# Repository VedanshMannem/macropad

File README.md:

# Setup

1) Set up [OPL Libary](https://github.com/Seeed-Studio/OPL_Kicad_Library/)
2) Add this for the [OLED footprints](https://gi1thub.com/gorbachev/KiCad-SSD1306-0.91-OLED-4pin-128x32.pretty/blob/master/SSD1306-0.91-OLED-4pin-128x32.kicad_mod)
3) Download all the project files into KiCad/Fusion or whatever system you use and you can edit however

Materials (No BOM):
- 4x Cherry MX Switches
- 6x SK6812 MINI Leds
- 1x XIAO RP2040
- 4x Blank DSA Keycaps
- 4x M3x16 Bolt
- 4x M3 Heatset
- 1x OLED 0.91in display

Schematic            |  PCB         |   Case
:-------------------------:|:-------------------------:|:-------------------------:|
 |   | 

First time CADding and second time doing PCBs. Learned lots about routing, edge cuts, and just general CADding.

Cool features:
- Macros for productivity (vibe coding)
- Layers for different modes to increase functionality
- Layeres: Volume/mute, productivity, WASD
- Switch between layers with 5s hold
- LED & OLED display showing different layers

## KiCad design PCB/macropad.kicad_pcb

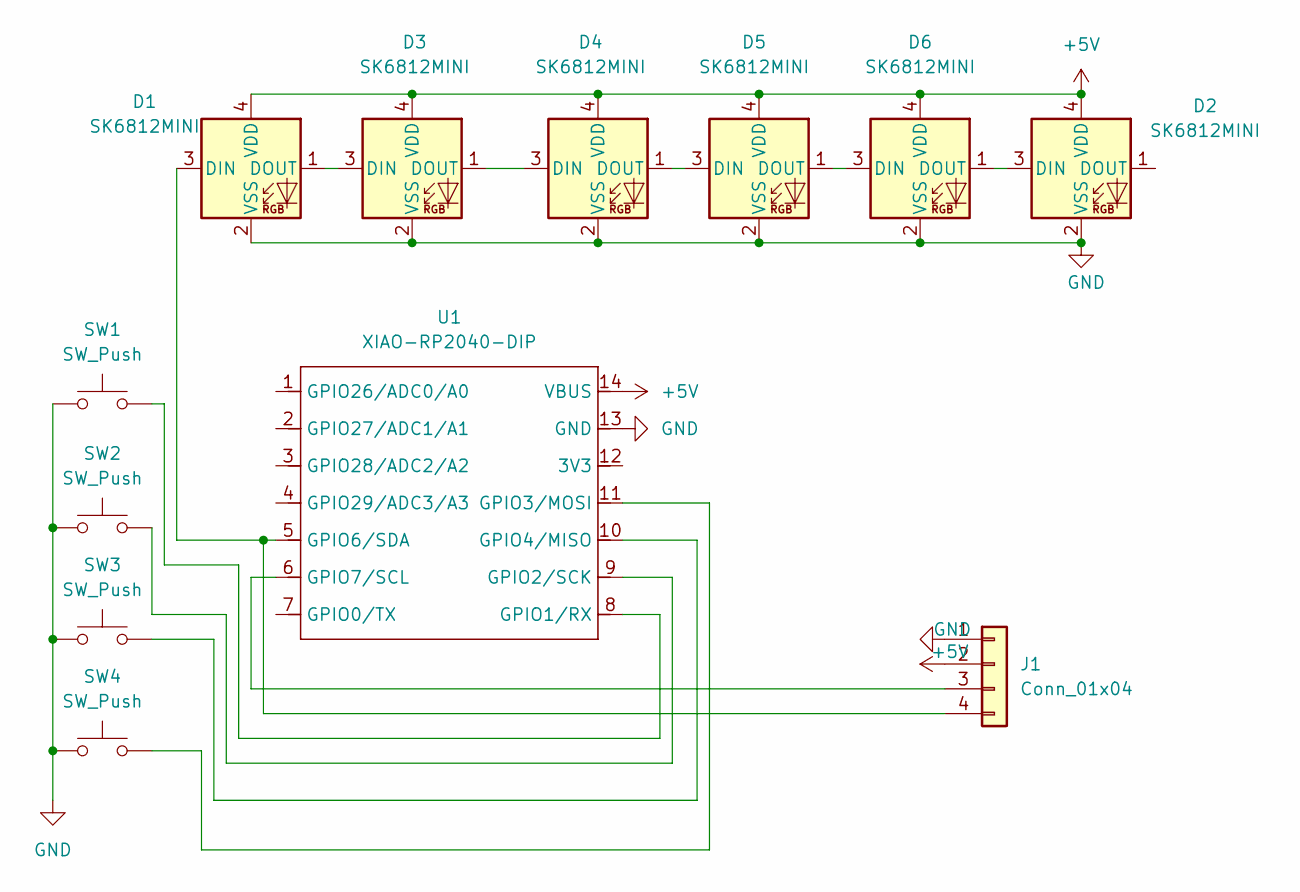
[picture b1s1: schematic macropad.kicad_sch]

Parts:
D1, D2, D3, D4, D5, D6: SK6812MINI; LED_SK6812MINI_PLCC4_3.5x3.5mm_P1.75mm
J1: Conn_01x04; SSD1306-0.91-OLED-4pin-128x32
SW1, SW2, SW3, SW4: SW_Push; SW_Cherry_MX_1.00u_PCB
U1: XIAO-RP2040-DIP

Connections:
+5V: D1.4 (VDD), D2.4 (VDD), D3.4 (VDD), D4.4 (VDD), D5.4 (VDD), D6.4 (VDD), J1.2, U1.14 (VBUS)
GND: D1.2 (VSS), D2.2 (VSS), D3.2 (VSS), D4.2 (VSS), D5.2 (VSS), D6.2 (VSS), J1.1, SW1.1, SW2.1, SW3.1, SW4.1, U1.13 (GND)
unnamed: D1.3 (DIN), J1.4, U1.5 (GPIO6/SDA)
unnamed: D1.1 (DOUT), D3.3 (DIN)
unnamed: D2.3 (DIN), D6.1 (DOUT)
unnamed: D3.1 (DOUT), D4.3 (DIN)
unnamed: D4.1 (DOUT), D5.3 (DIN)
unnamed: D5.1 (DOUT), D6.3 (DIN)
unnamed: J1.3, U1.6 (GPIO7/SCL)
unnamed: SW1.2, U1.8 (GPIO1/RX)
unnamed: SW2.2, U1.9 (GPIO2/SCK)
unnamed: SW4.2, U1.11 (GPIO3/MOSI)
unnamed: SW3.2, U1.10 (GPIO4/MISO)

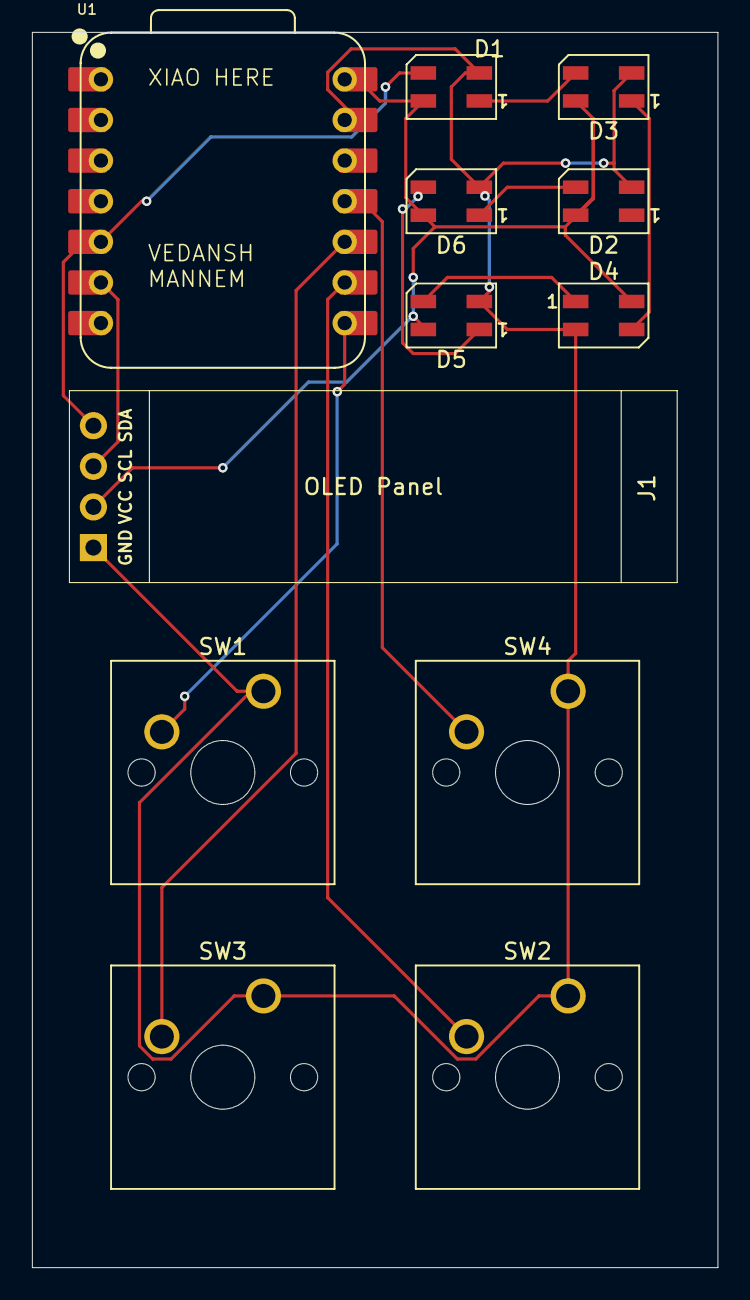
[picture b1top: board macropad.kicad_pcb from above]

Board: 2 copper layers, 42.9 x 77.2 mm, 12 parts (0 on the bottom side), 13 nets.

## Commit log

2025-11-22 bottom case
2025-11-24 cad + pcb
2025-11-24 Add placeholder.txt with initial content
2025-11-24 adding hackpad
2025-11-24 Add placeholder file with a single character
2025-11-24 Main kicad files
2025-11-24 Update README with materials and features
    Added additional images and a section on cool features.
2025-11-24 Initialize KMK keyboard with display and macros
